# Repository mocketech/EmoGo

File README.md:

# EmoGo
A Go game system that conveys the state of Go stones through facial expressions

概要は以下の記事をご覧下さい。

Protopedia: [情碁 - 碁石の状態を表情で伝える囲碁ゲームシステム](https://protopedia.net/prototype/6237)

You can refer the following sites:
* Qiita: [XIAO RP2040でXIAO Round Displayを使う](https://qiita.com/mocketech/items/0c186354648cb941cb2cl) (in Japanese)
* [Seeed Studio XIAO RP2040 with Arduino](https://wiki.seeedstudio.com/XIAO-RP2040-with-Arduino/)
* [Getting Started with Seeed Studio Round Display for XIAO](https://wiki.seeedstudio.com/get_start_round_display/)
* Github: [MCP_CAN_lib](https://github.com/coryjfowler/MCP_CAN_lib)
* Waveshare: [2-CH CAN HAT](https://www.waveshare.com/wiki/2-CH_CAN_HAT)

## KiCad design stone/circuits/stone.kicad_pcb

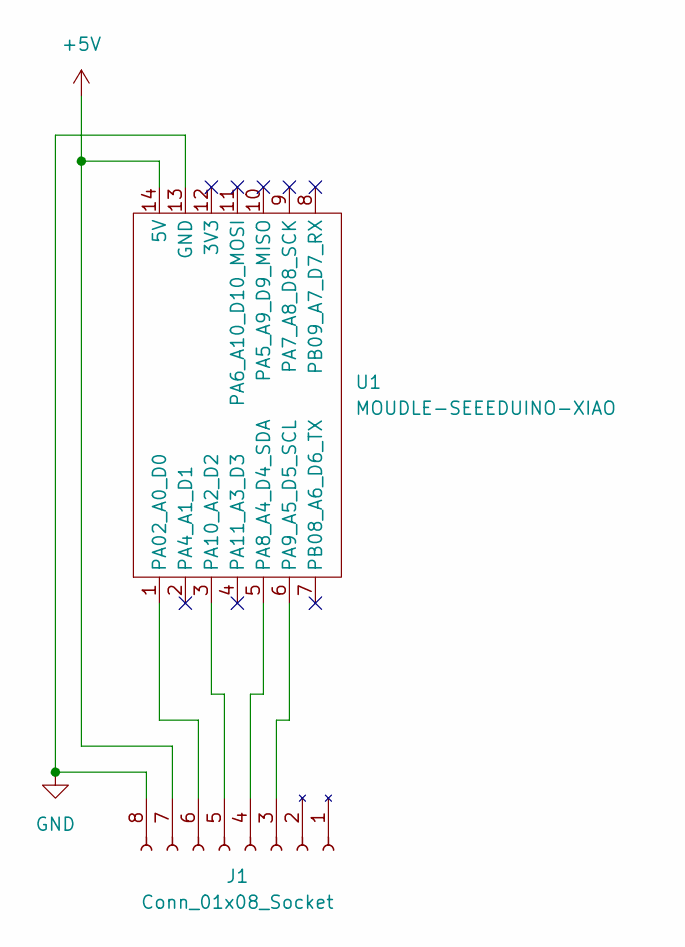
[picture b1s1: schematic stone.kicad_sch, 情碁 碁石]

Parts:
J1: Conn_01x08_Socket; PinSocket_1x08_P2.54mm_Vertical
U1: MOUDLE-SEEEDUINO-XIAO; MOUDLE14P-2.54-21X17.8MM

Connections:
+5V: J1.7, U1.14 (5V)
GND: J1.8, U1.13 (GND)
unnamed: J1.3, U1.6 (PA9_A5_D5_SCL)
unnamed: J1.4, U1.5 (PA8_A4_D4_SDA)
unnamed: J1.5, U1.3 (PA10_A2_D2)
unnamed: J1.6, U1.1 (PA02_A0_D0)

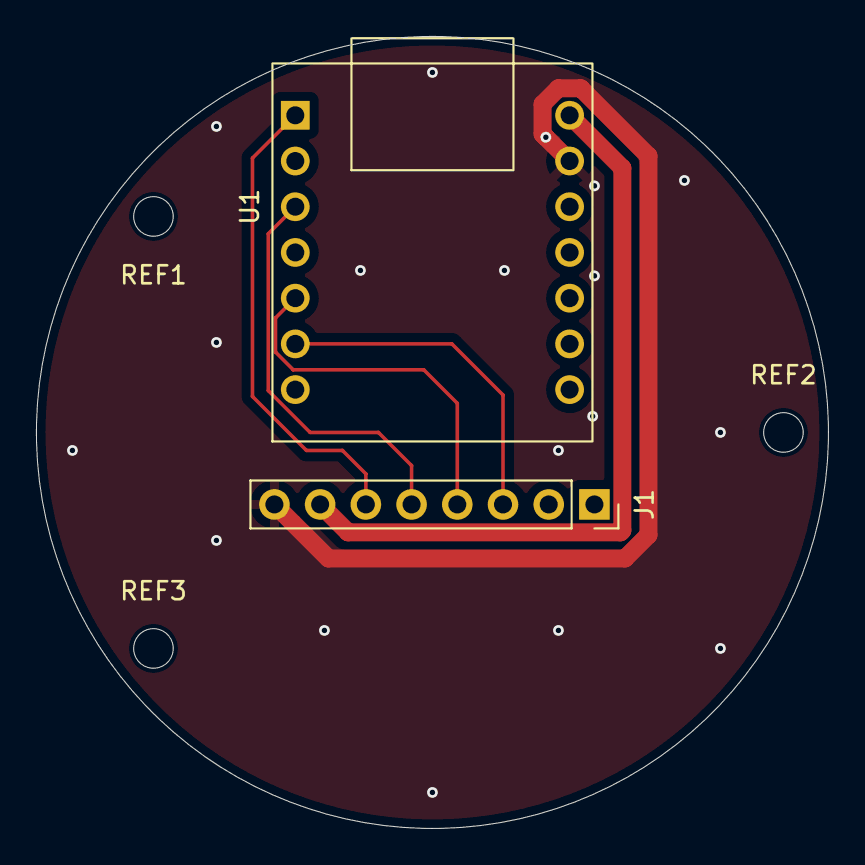
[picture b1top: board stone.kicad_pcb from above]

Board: 2 copper layers, 44.0 x 44.0 mm, 5 parts (0 on the bottom side), 6 nets.

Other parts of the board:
REF1, REF2, REF3: MountingHole_2.2mm_M2

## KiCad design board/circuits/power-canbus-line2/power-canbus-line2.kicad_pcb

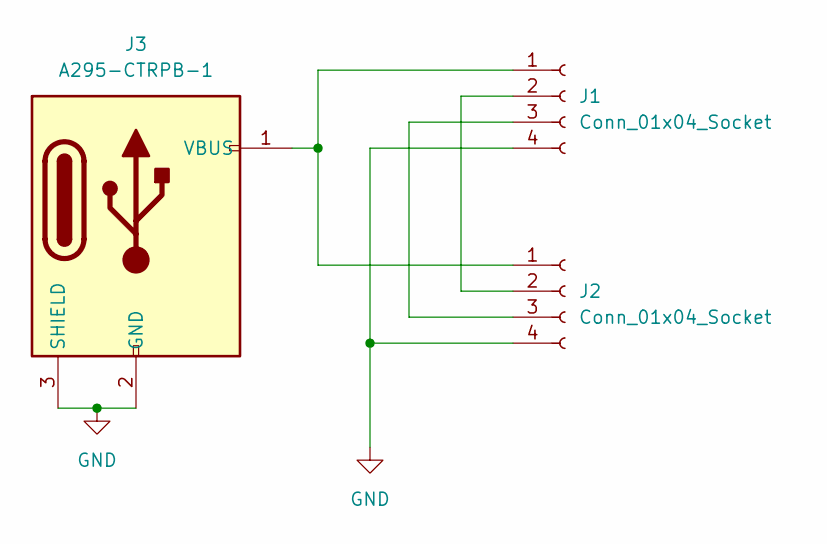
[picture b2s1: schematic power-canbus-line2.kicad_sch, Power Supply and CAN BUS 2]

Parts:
J1, J2: Conn_01x04_Socket; PinSocket_1x04_P2.54mm_Horizontal
J3: A295-CTRPB-1

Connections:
GND: J1.4, J2.4, J3.2 (GND), J3.3 (SHIELD)
unnamed: J1.1, J2.1, J3.1 (VBUS)
unnamed: J1.2, J2.2
unnamed: J1.3, J2.3

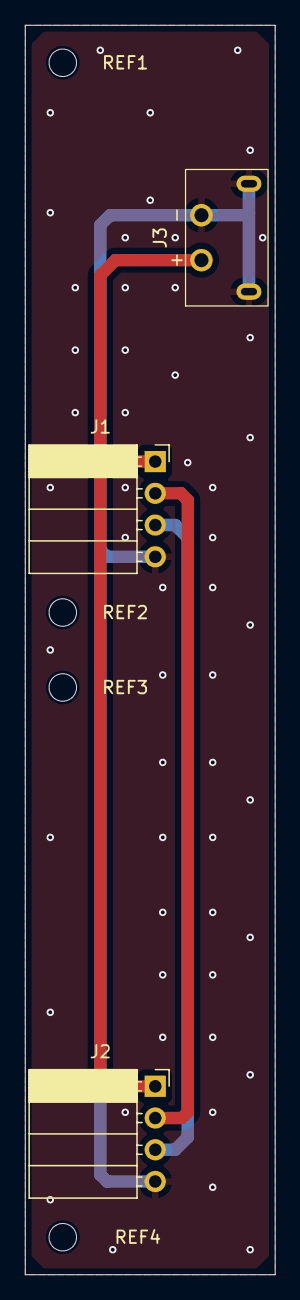
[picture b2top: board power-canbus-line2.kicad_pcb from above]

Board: 2 copper layers, 20.0 x 100.0 mm, 7 parts (0 on the bottom side), 4 nets.

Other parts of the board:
REF1, REF2, REF3: MountingHole_2.2mm_M2_DIN965
REF4: MountingHole_2.2mm_M2

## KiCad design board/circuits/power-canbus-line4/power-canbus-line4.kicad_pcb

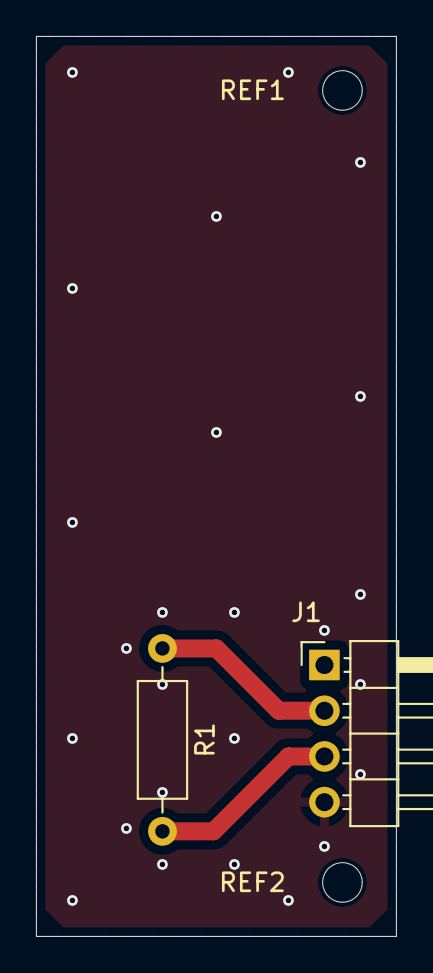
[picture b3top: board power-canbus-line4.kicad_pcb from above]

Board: 2 copper layers, 20.0 x 50.0 mm, 4 parts (0 on the bottom side), 2 nets.

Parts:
J1: Conn_01x04_Pin; PinHeader_1x04_P2.54mm_Horizontal
R1: 120; R_Axial_DIN0207_L6.3mm_D2.5mm_P10.16mm_Horizontal
REF1, REF2: MountingHole_2.2mm_M2_DIN965

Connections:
unnamed: J1.2, R1.1
unnamed: J1.3, R1.2

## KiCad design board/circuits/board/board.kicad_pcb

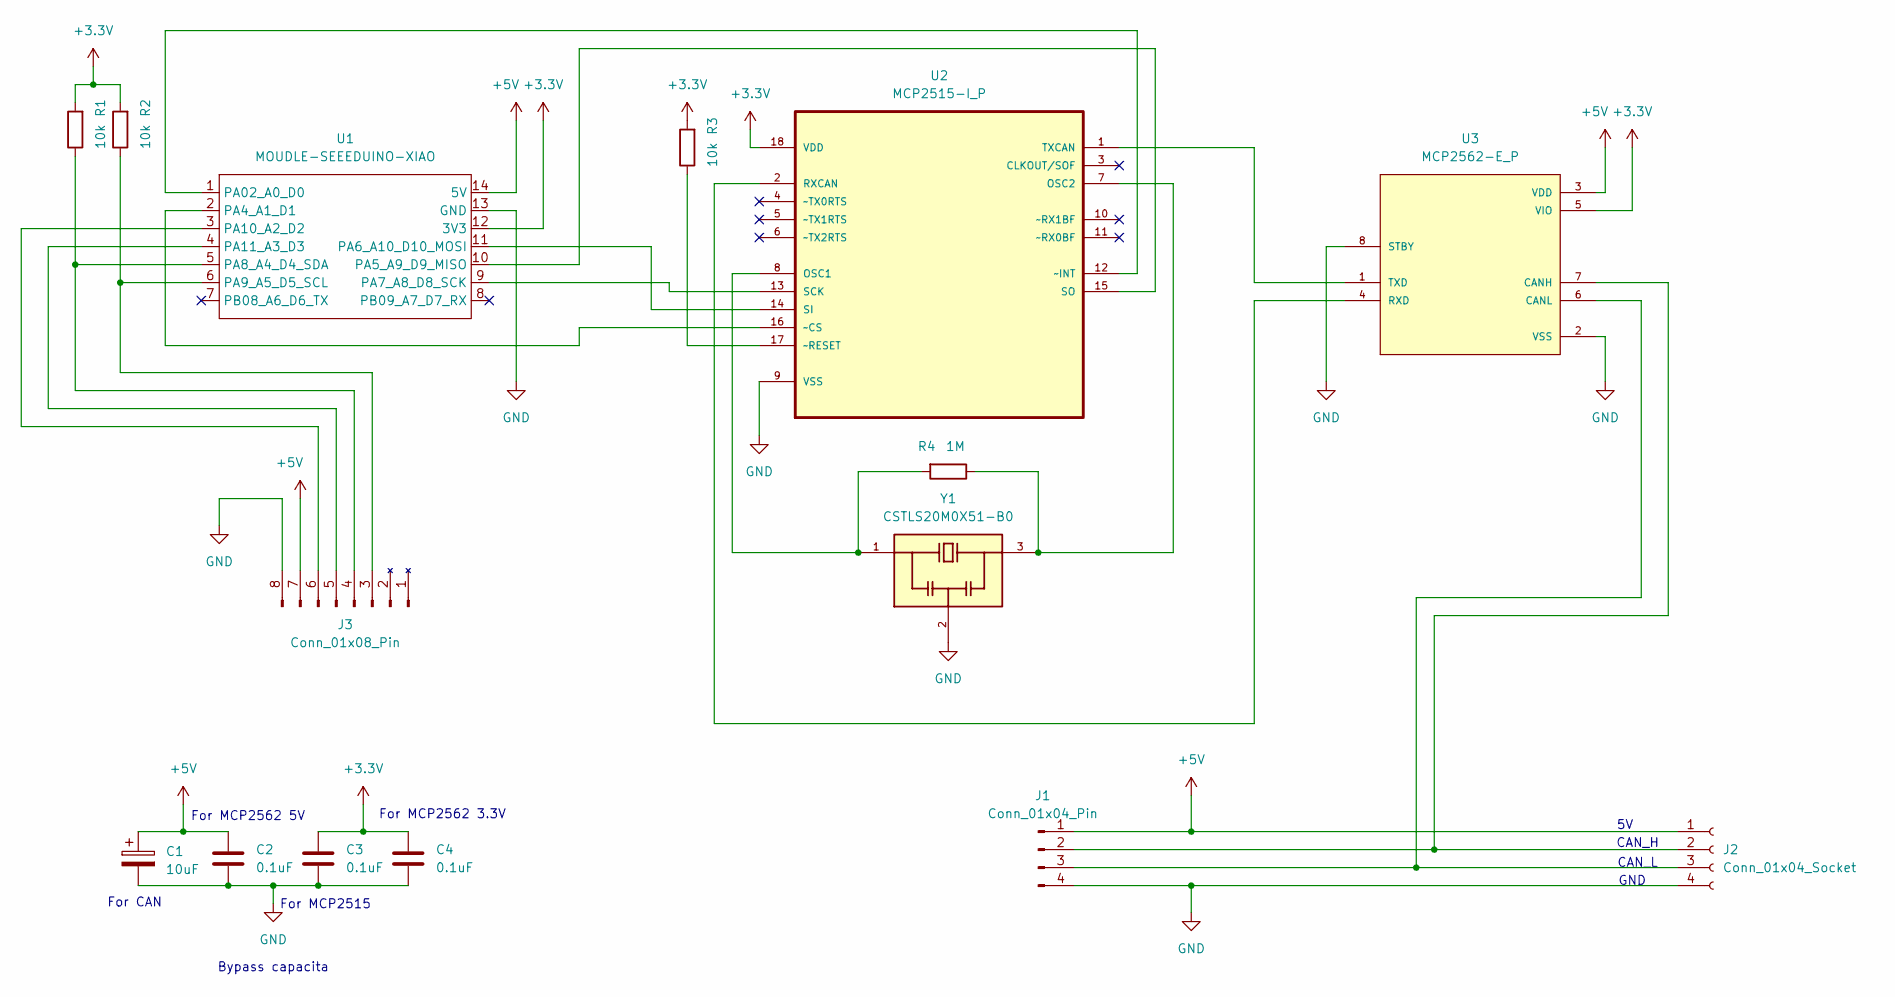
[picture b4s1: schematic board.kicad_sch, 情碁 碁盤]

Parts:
C1: 10uF; CP_Radial_D4.0mm_P1.50mm
C2, C3, C4: 0.1uF; C_Disc_D3.8mm_W2.6mm_P2.50mm
J1: Conn_01x04_Pin; PinHeader_1x04_P2.54mm_Horizontal
J2: Conn_01x04_Socket; PinSocket_1x04_P2.54mm_Horizontal
J3: Conn_01x08_Pin; PinHeader_1x08_P2.54mm_Vertical
R1, R2, R3: 10k; R_Axial_DIN0207_L6.3mm_D2.5mm_P10.16mm_Horizontal
R4: 1M; R_Axial_DIN0207_L6.3mm_D2.5mm_P10.16mm_Horizontal
U1: MOUDLE-SEEEDUINO-XIAO; MOUDLE14P-SMD-2.54-21X17.8MM
U2: MCP2515-I_P; DIP254P762X432-18; MPN MCP2515-I/P
U3: MCP2562-E_P; DIP787W45P254L1016H533Q8; PARTREV C
Y1: CSTLS20M0X51-B0; OSC_CSTLS20M0X51-B0; PARTREV March 23, 2017

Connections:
+3.3V: C3.1, C4.1, R1.2, R2.2, R3.2, U1.12 (3V3), U2.18 (VDD), U3.5 (VIO)
+5V: C1.1, C2.1, J1.1 (5V), J2.1 (5V), J3.7, U1.14 (5V), U3.3 (VDD)
GND: C1.2, C2.2, C3.2, C4.2, J1.4 (GND), J2.4 (GND), J3.8, U1.13 (GND), U2.9 (VSS), U3.2 (VSS), U3.8 (STBY), Y1.2
unnamed: J1.2 (CAN_H), J2.2 (CAN_H), U3.7 (CANH)
unnamed: J1.3 (CAN_L), J2.3 (CAN_L), U3.6 (CANL)
unnamed: J3.3, R2.1, U1.6 (PA9_A5_D5_SCL)
unnamed: J3.4, R1.1, U1.5 (PA8_A4_D4_SDA)
unnamed: J3.5, U1.4 (PA11_A3_D3)
unnamed: J3.6, U1.3 (PA10_A2_D2)
unnamed: U1.1 (PA02_A0_D0), U2.12 (~INT)
unnamed: U1.2 (PA4_A1_D1), U2.16 (~CS)
unnamed: U1.10 (PA5_A9_D9_MISO), U2.15 (SO)
unnamed: U1.11 (PA6_A10_D10_MOSI), U2.14 (SI)
unnamed: U1.9 (PA7_A8_D8_SCK), U2.13 (SCK)
unnamed: R4.2, U2.8 (OSC1), Y1.1
unnamed: R4.1, U2.7 (OSC2), Y1.3
unnamed: U2.2 (RXCAN), U3.4 (RXD)
unnamed: U2.1 (TXCAN), U3.1 (TXD)
unnamed: R3.1, U2.17 (~RESET)

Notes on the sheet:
For CAN
For MCP2515
For MCP2562 3.3V
GND
Bypass capacita
CAN_H
CAN_L
For MCP2562 5V

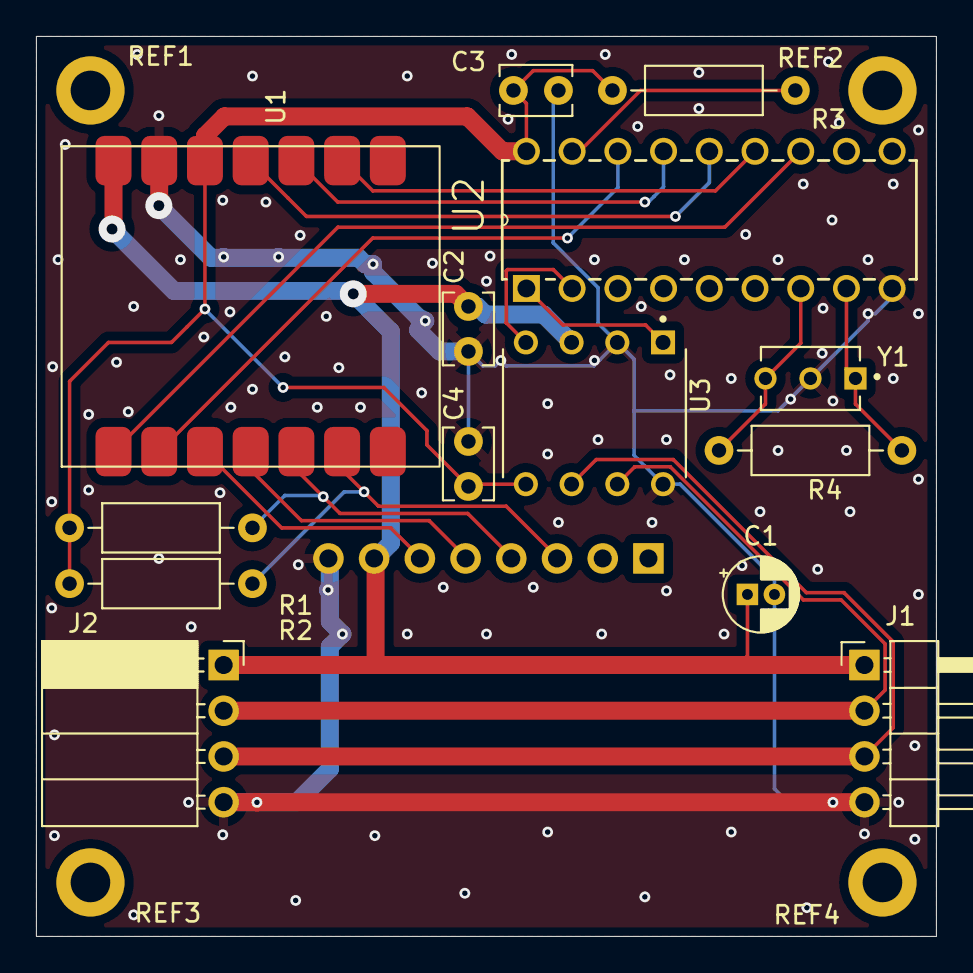
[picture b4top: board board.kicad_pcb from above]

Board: 2 copper layers, 50.0 x 50.0 mm, 19 parts (1 on the bottom side), 19 nets.

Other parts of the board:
REF1, REF2, REF3, REF4: MountingHole_2.2mm_M2_DIN965_Pad

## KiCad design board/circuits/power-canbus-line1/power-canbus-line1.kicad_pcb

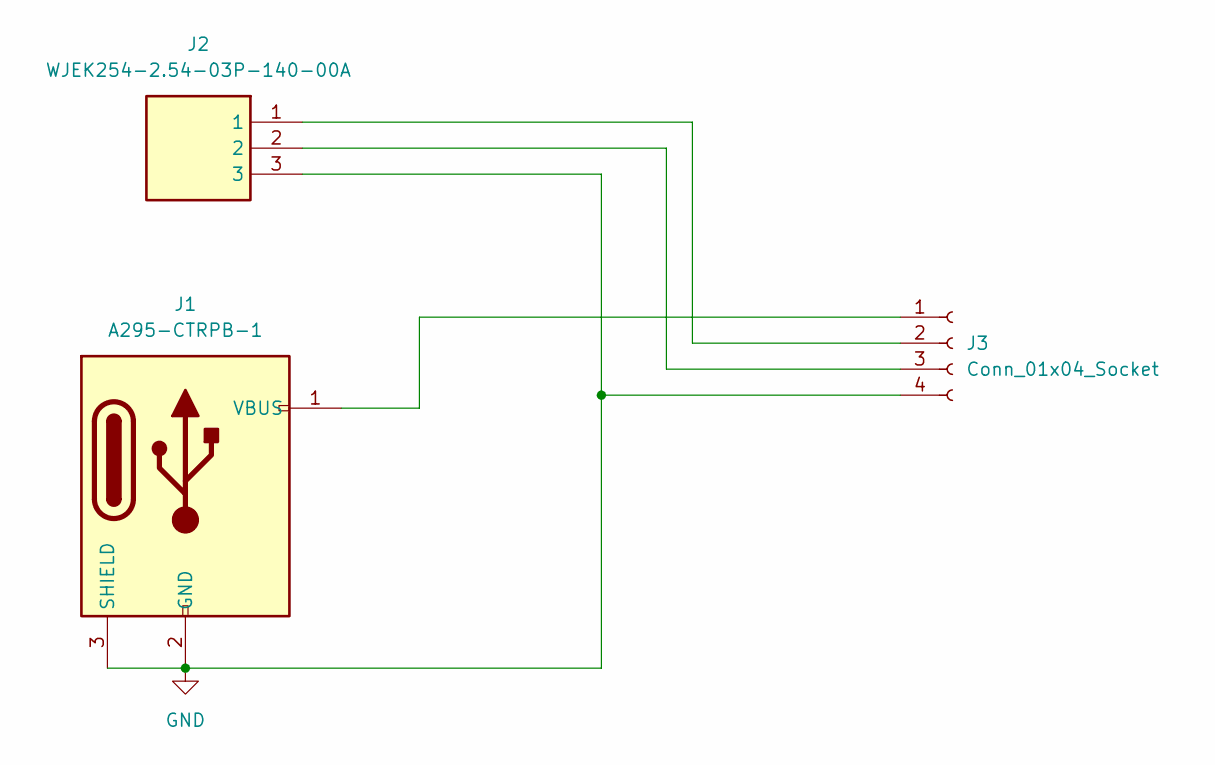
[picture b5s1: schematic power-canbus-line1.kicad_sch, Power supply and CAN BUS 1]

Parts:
J1: A295-CTRPB-1
J2: WJEK254-2.54-03P-140-00A; WJEK25425403P14000A; Manufacturer_Part_Number WJEK254-2.54-03P-140-00A
J3: Conn_01x04_Socket; PinSocket_1x04_P2.54mm_Horizontal

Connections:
GND: J1.2 (GND), J1.3 (SHIELD), J2.3, J3.4
unnamed: J1.1 (VBUS), J3.1
unnamed: J2.1, J3.2
unnamed: J2.2, J3.3

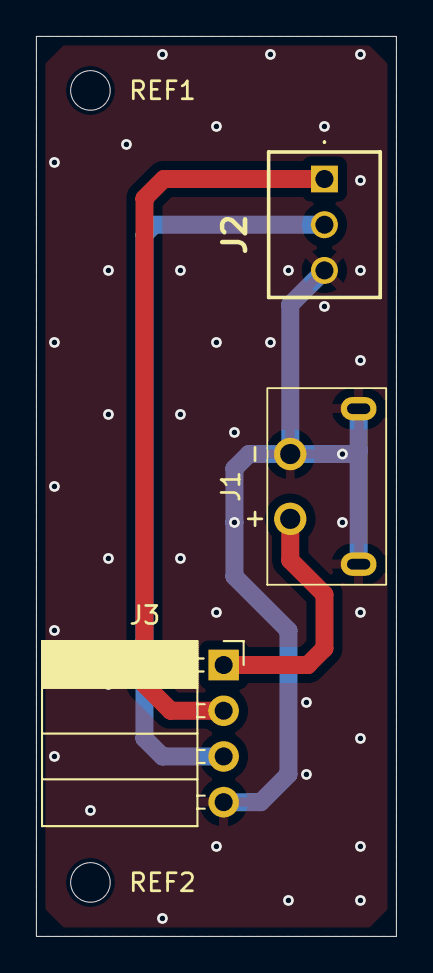
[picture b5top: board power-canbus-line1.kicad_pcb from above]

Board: 2 copper layers, 20.0 x 50.0 mm, 5 parts (0 on the bottom side), 4 nets.

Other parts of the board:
REF1, REF2: MountingHole_2.2mm_M2_DIN965

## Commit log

2024-12-10 Initial commit.
2025-03-04 Update README.md
    Add references.
